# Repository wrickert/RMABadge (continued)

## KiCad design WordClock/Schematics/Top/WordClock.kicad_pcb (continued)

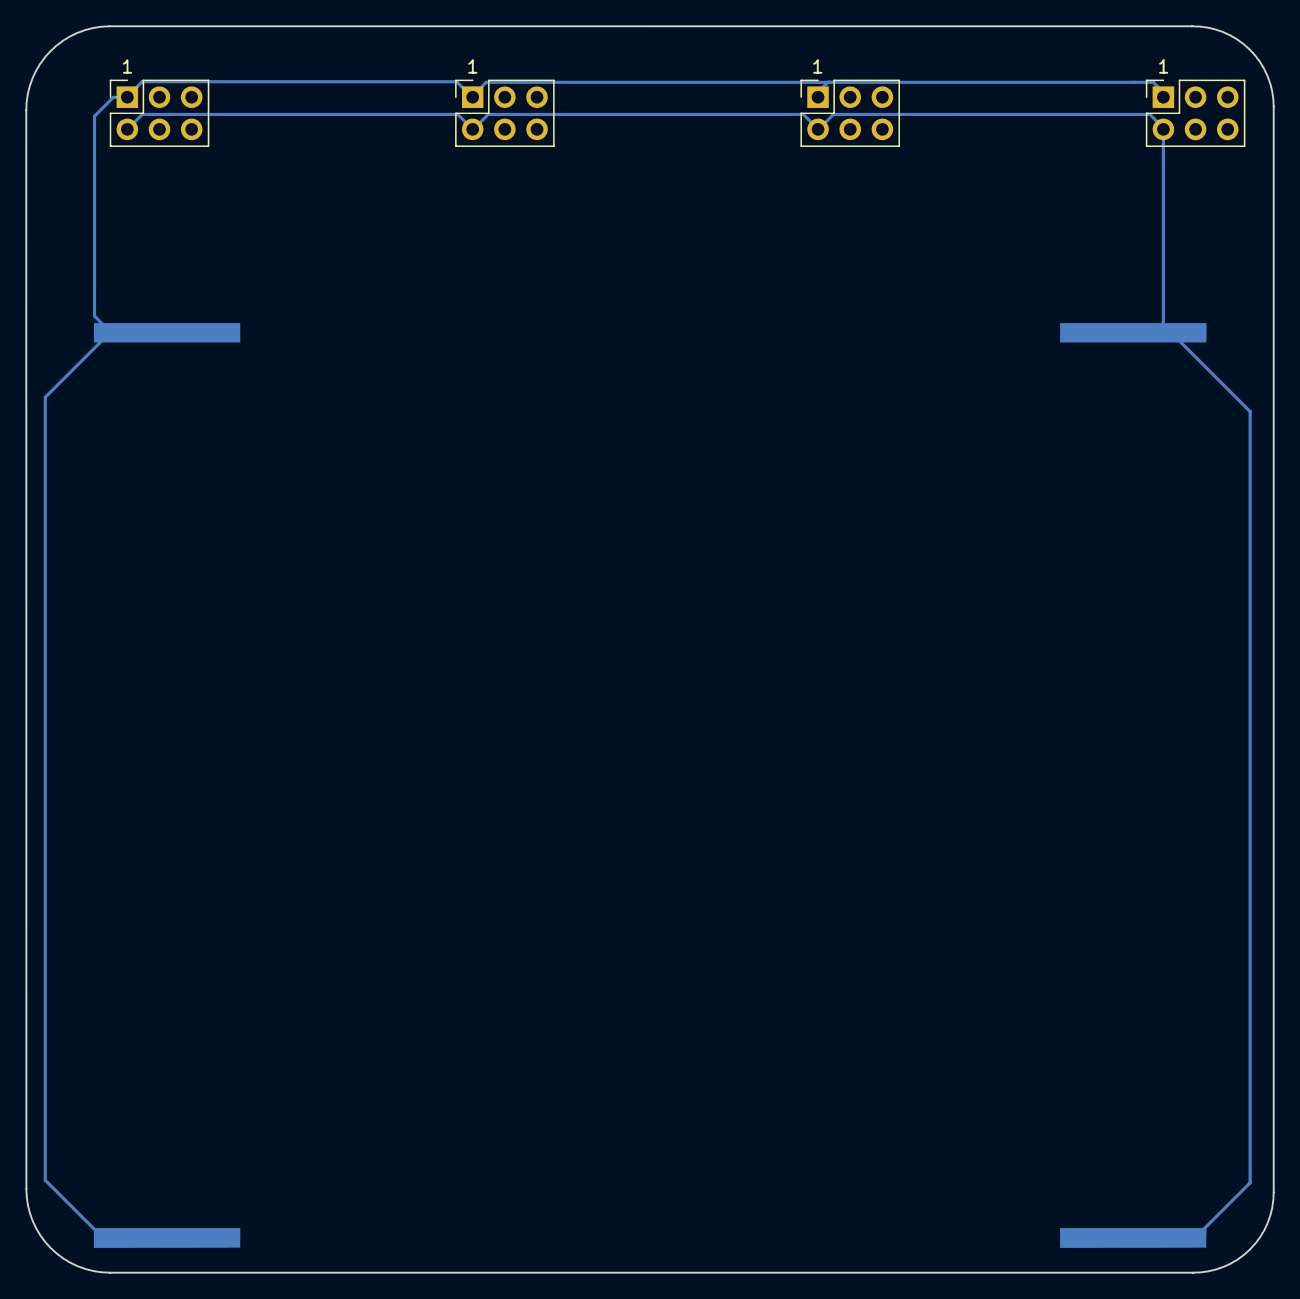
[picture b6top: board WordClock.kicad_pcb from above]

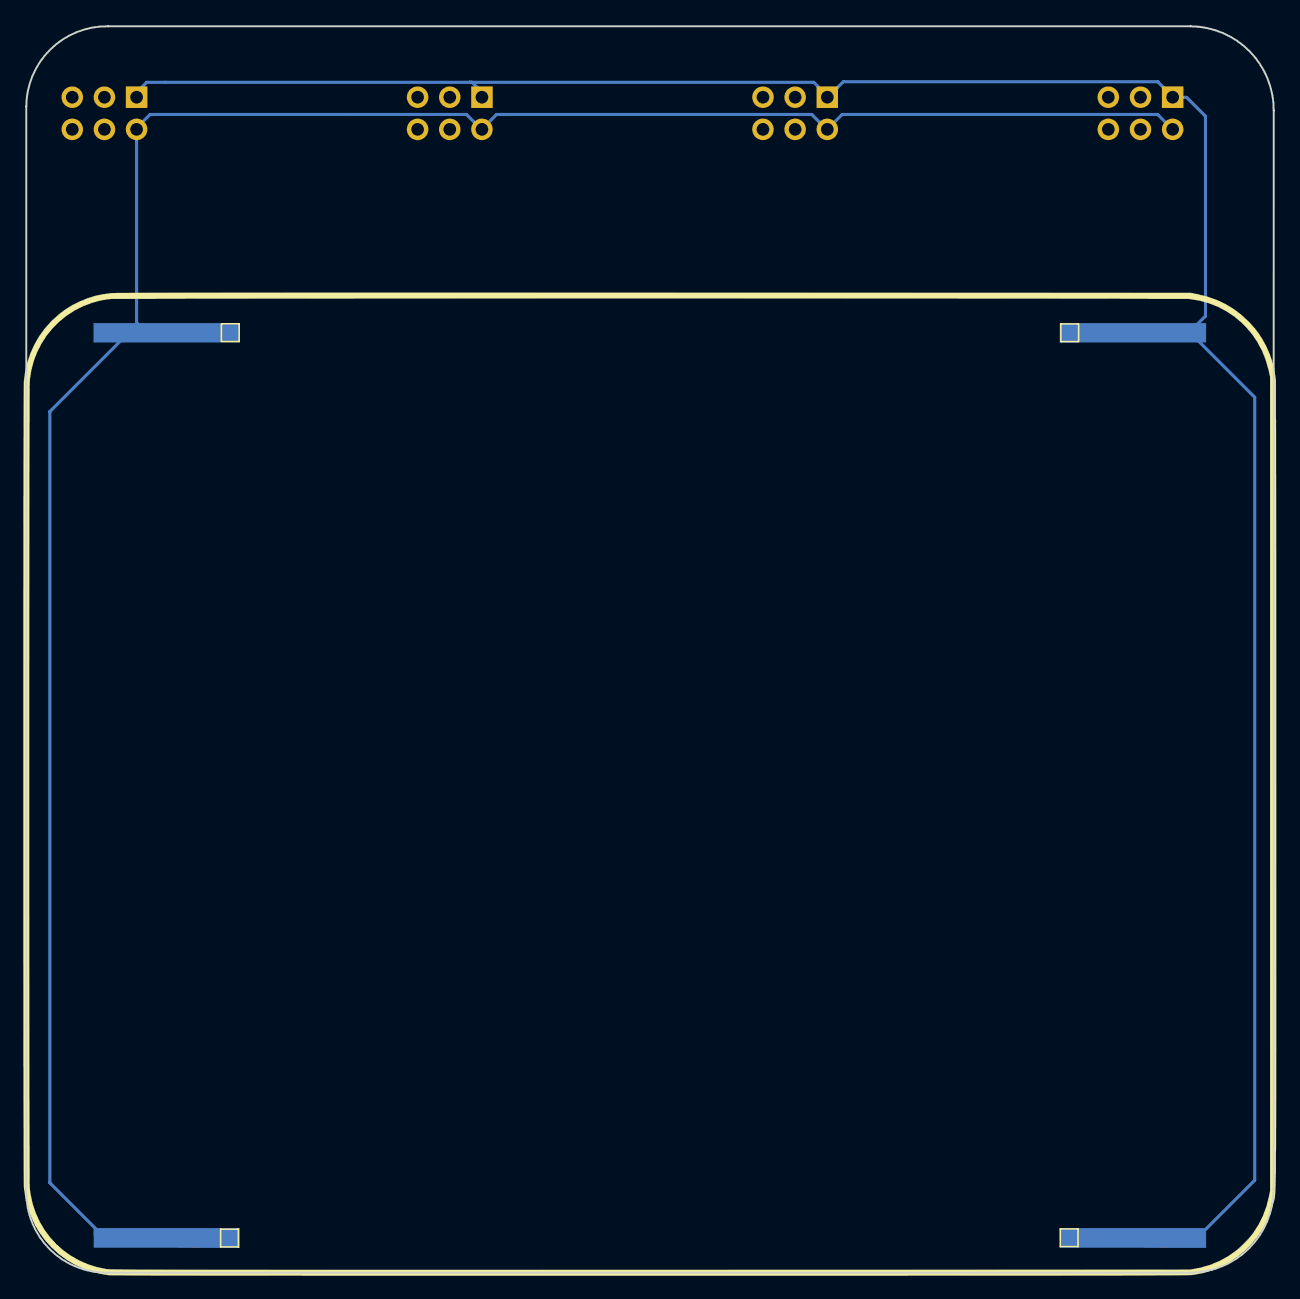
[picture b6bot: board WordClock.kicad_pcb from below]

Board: 2 copper layers, 98.5 x 98.4 mm, 8 parts (4 on the bottom side), 2 nets.
